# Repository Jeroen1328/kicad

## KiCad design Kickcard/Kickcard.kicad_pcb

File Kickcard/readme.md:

## The "KickCard": External Kickstart Freedom for the Amiga 500 🚀

The **KickCard** project was born out of a common frustration among **Amiga 500** enthusiasts: the hassle and motherboard variations involved in upgrading the internal **Kickstart ROM**. This external interface, connected via the Amiga 500's side expansion slot, offers a clean, versatile, and non-intrusive solution for using different Kickstart ROMs.

### Status
This project is **currently under construction** and has **not been tested** in a physical unit. The author is uncertain if a functional board will ultimately be built.

---

### Overcoming Internal ROM Challenges

Older Amiga 500 revisions required specific circuitry, often involving **pull-up resistors** on the data bus, to properly support certain **EPROMs** when used as the Kickstart ROM. Installing a new ROM meant opening the computer, desoldering (sometimes), and potentially adding components.

The KickCard eliminates this complexity. By providing an **external, standardized interface**, it bypasses the finicky requirements of various motherboard revisions, making ROM upgrades plug-and-play. Plus, you never have to **open your Amiga 500** just to swap a Kickstart version!

---

### Features and Functionality

Beyond its core function, the KickCard is a feature-rich expansion:

* **External Enable/Disable:** A DIP switch (**SW\_KICK**) allows the user to easily **enable or disable** the external KickCard ROM, reverting to the internal ROM if present.
* **Monitoring and Control (Optional):**
    * **Voltmeters:** Three optional **voltmeters** display the Amiga's crucial **+5V, +12V, and -12V** power supply lines, providing immediate diagnostic feedback.
    * **NMI/Reset Buttons:** Optional buttons for **$\overline{\text{INT7}}$ (Non-Maskable Interrupt)** and **System Reset** offer convenient control without needing a software-based utility.

---

### How the KickCard Works (The Logic)

The core of the KickCard's operation relies on a **GAL (Generic Array Logic)** chip and the Amiga's memory management architecture:

1.  **Initial Activation:** When the Amiga system starts up or is reset, a specific register, **$\overline{\text{OVL}}$ (Overlay)**, becomes active.
2.  **Memory Access Interception:** When the CPU addresses the **Kickstart memory range** ($000000-\text{07FFFF}$ and $\text{F80000}-\text{FFFFFF}$) with $\overline{\text{OVL}}$ active or ($\text{F80000}-\text{FFFFFF}$) with $\overline{\text{OVL}}$ not active, the GAL asserts the **$\overline{\text{OVR}}$ (Override)** signal.
3.  **Gary Disablement:** The asserted $\overline{\text{OVR}}$ signal prevents the **GARY** (Gate Array) chip—which typically manages memory arbitration—from responding to the bus, effectively taking control of the Kickstart address space.
4.  **Deactivation:** The $\overline{\text{OVL}}$ remains active until the CPU executes a write access to the address of the **CIA (Complex Interface Adapter)** chips. This action typically signals the completion of the basic system startup, and the GAL then makes the $\overline{\text{OVL}}$ register **inactive**, returning memory control to the standard system configuration.
5.  **when the roms is selected, the GAL also asserts the $\overline{\text{DTACK}}$ signal to tell the 68000 to complete the read cycle.
 
In essence, the KickCard *tricks* the Amiga into loading the Kickstart from the expansion port during the critical boot sequence, providing a robust and flexible ROM replacement solution.

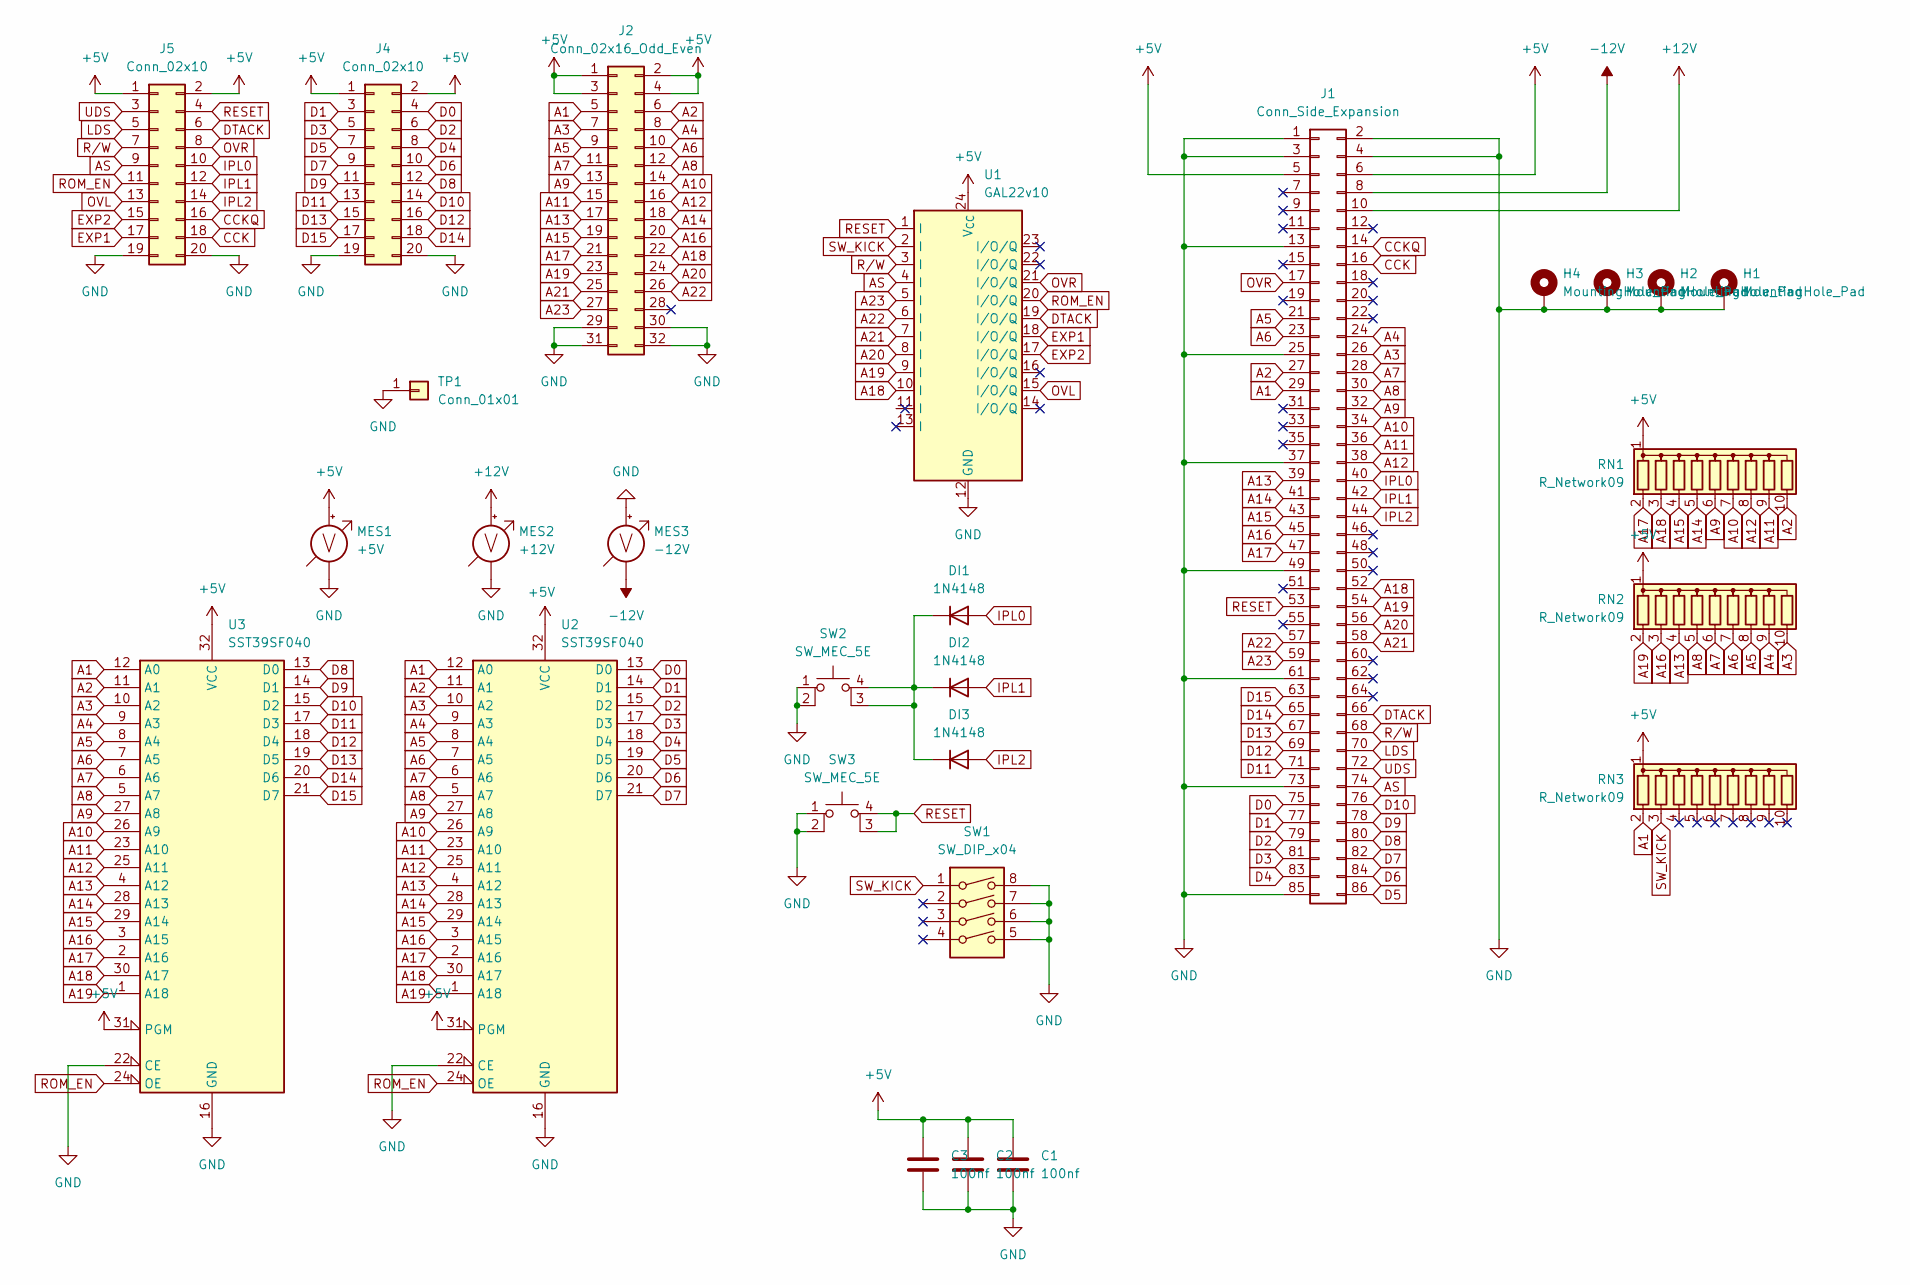
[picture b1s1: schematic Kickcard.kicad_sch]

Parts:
C1, C2, C3: 100nf; C_Disc_D3.0mm_W1.6mm_P2.50mm
DI1, DI2, DI3: 1N4148; D_DO-35_SOD27_P7.62mm_Horizontal
H1, H2, H3, H4: MountingHole_Pad; MountingHole_3.2mm_M3_Pad_Via
J1: Conn_Side_Expansion; Conn_Side_Expansion_Vertical
J2: Conn_02x16_Odd_Even; PinHeader_2x16_P2.54mm_Vertical
J4, J5: Conn_02x10; PinHeader_2x10_P2.54mm_Vertical
MES1: +5V; 0.28 voltmeter
MES2: +12V; 0.28 voltmeter
MES3: -12V; 0.28 voltmeter
RN1, RN2, RN3: R_Network09; R_Array_SIP10
SW1: SW_DIP_x04; SW_DIP_SPSTx04_Slide_6.7x11.72mm_W7.62mm_P2.54mm_LowProfile
SW2, SW3: SW_MEC_5E; Tactile Switch
TP1: Conn_01x01; TestPoint_Bridge_Pitch2.54mm_Drill1.0mm
U1: GAL22v10; DIP-24_W7.62mm
U2, U3: SST39SF040; DIP-32_W15.24mm

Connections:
+5V: C1.1, C2.1, C3.1, J1.5 (+5V), J1.6 (+5V), J2.1, J2.2, J2.3, J2.4, J4.1, J4.2, J5.1, J5.2, MES1.2 (+), RN1.1 (common), RN2.1 (common), RN3.1 (common), U1.24 (V_{CC}), U2.31 (PGM), U2.32 (VCC), U3.31 (PGM), U3.32 (VCC)
+12V: J1.10 (+12V), MES2.2 (+)
-12V: J1.8 (-5V), MES3.1 (-)
A1: J1.29 (A1), J2.5, RN3.2 (R1), U2.12 (A0), U3.12 (A0)
A2: J1.27 (A2), J2.6, RN1.10 (R9), U2.11 (A1), U3.11 (A1)
A3: J1.26 (A3), J2.7, RN2.10 (R9), U2.10 (A2), U3.10 (A2)
A4: J1.24 (A4), J2.8, RN2.9 (R8), U2.9 (A3), U3.9 (A3)
A5: J1.21 (A5), J2.9, RN2.8 (R7), U2.8 (A4), U3.8 (A4)
A6: J1.23 (A6), J2.10, RN2.7 (R6), U2.7 (A5), U3.7 (A5)
A7: J1.28 (A7), J2.11, RN2.6 (R5), U2.6 (A6), U3.6 (A6)
A8: J1.30 (A8), J2.12, RN2.5 (R4), U2.5 (A7), U3.5 (A7)
A9: J1.32 (A9), J2.13, RN1.6 (R5), U2.27 (A8), U3.27 (A8)
A10: J1.34 (A10), J2.14, RN1.7 (R6), U2.26 (A9), U3.26 (A9)
A11: J1.36 (A11), J2.15, RN1.9 (R8), U2.23 (A10), U3.23 (A10)
A12: J1.38 (A12), J2.16, RN1.8 (R7), U2.25 (A11), U3.25 (A11)
A13: J1.39 (A13), J2.17, RN2.4 (R3), U2.4 (A12), U3.4 (A12)
A14: J1.41 (A14), J2.18, RN1.5 (R4), U2.28 (A13), U3.28 (A13)
A15: J1.43 (A15), J2.19, RN1.4 (R3), U2.29 (A14), U3.29 (A14)
A16: J1.45 (A16), J2.20, RN2.3 (R2), U2.3 (A15), U3.3 (A15)
A17: J1.47 (A17), J2.21, RN1.2 (R1), U2.2 (A16), U3.2 (A16)
A18: J1.52 (A18), J2.22, RN1.3 (R2), U1.10 (I), U2.30 (A17), U3.30 (A17)
A19: J1.54 (A19), J2.23, RN2.2 (R1), U1.9 (I), U2.1 (A18), U3.1 (A18)
A20: J1.56 (A20), J2.24, U1.8 (I)
A21: J1.58 (A22), J2.25, U1.7 (I)
A22: J1.57 (A21), J2.26, U1.6 (I)
A23: J1.59 (A23), J2.27, U1.5 (I)
AS: J1.74 (_AS), J5.9, U1.4 (I)
CCK: J1.16 (XRDY), J5.18
CCKQ: J1.14 (_CCKQ), J5.16
D0: J1.75 (PD0), J4.4, U2.13 (D0)
D1: J1.77 (PD1), J4.3, U2.14 (D1)
D2: J1.79 (PD2), J4.6, U2.15 (D2)
D3: J1.81 (PD3), J4.5, U2.17 (D3)
D4: J1.83 (PD4), J4.8, U2.18 (D4)
D5: J1.86 (PD5), J4.7, U2.19 (D5)
D6: J1.84 (PD6), J4.10, U2.20 (D6)
D7: J1.82 (PD7), J4.9, U2.21 (D7)
D8: J1.80 (PD8), J4.12, U3.13 (D0)
D9: J1.78 (PD9), J4.11, U3.14 (D1)
D10: J1.76 (PD10), J4.14, U3.15 (D2)
D11: J1.71 (PD11), J4.13, U3.17 (D3)
D12: J1.69 (PD12), J4.16, U3.18 (D4)
D13: J1.67 (PD13), J4.15, U3.19 (D5)
D14: J1.65 (PD14), J4.18, U3.20 (D6)
D15: J1.63 (PD15), J4.17, U3.21 (D7)
DTACK: J1.66 (_DTACK), J5.6, U1.19 (I/O/Q)
EXP1: J5.17, U1.18 (I/O/Q)
EXP2: J5.15, U1.17 (I/O/Q)
GND: C1.2, C2.2, C3.2, H1.1, H2.1, H3.1, H4.1, J1.1 (GND), J1.2 (GND), J1.3 (GND), J1.4 (GND), J1.13 (GND), J1.25 (GND), J1.37 (GND), J1.49 (GND), J1.61 (GND), J1.73 (GND), J1.85 (GND), J2.29, J2.30, J2.31, J2.32, J4.19, J4.20, J5.19, J5.20, MES1.1 (-), MES2.1 (-), MES3.2 (+), SW1.5, SW1.6, SW1.7, SW1.8, SW2.1, SW2.2, SW3.1, SW3.2, TP1.1, U1.12 (GND), U2.16 (GND), U2.22 (CE), U3.16 (GND), U3.22 (CE)
IPL0: DI1.2 (A), J1.40 (_IPL0), J5.10
IPL1: DI2.2 (A), J1.42 (_IPL1), J5.12
IPL2: DI3.2 (A), J1.44 (_IPL2), J5.14
LDS: J1.70 (_LDS), J5.5
unnamed: DI1.1 (K), DI2.1 (K), DI3.1 (K), SW2.3 (K), SW2.4 (A)
OVL: J5.13, U1.15 (I/O/Q)
OVR: J1.17 (CDAC), J5.8, U1.21 (I/O/Q)
RESET: J1.53 (_RST), J5.4, SW3.3 (K), SW3.4 (A), U1.1 (I)
ROM_EN: J5.11, U1.20 (I/O/Q), U2.24 (OE), U3.24 (OE)
R/W: J1.68 (R_W), J5.7, U1.3 (I)
SW_KICK: RN3.3 (R2), SW1.1, U1.2 (I)
UDS: J1.72 (_UDS), J5.3

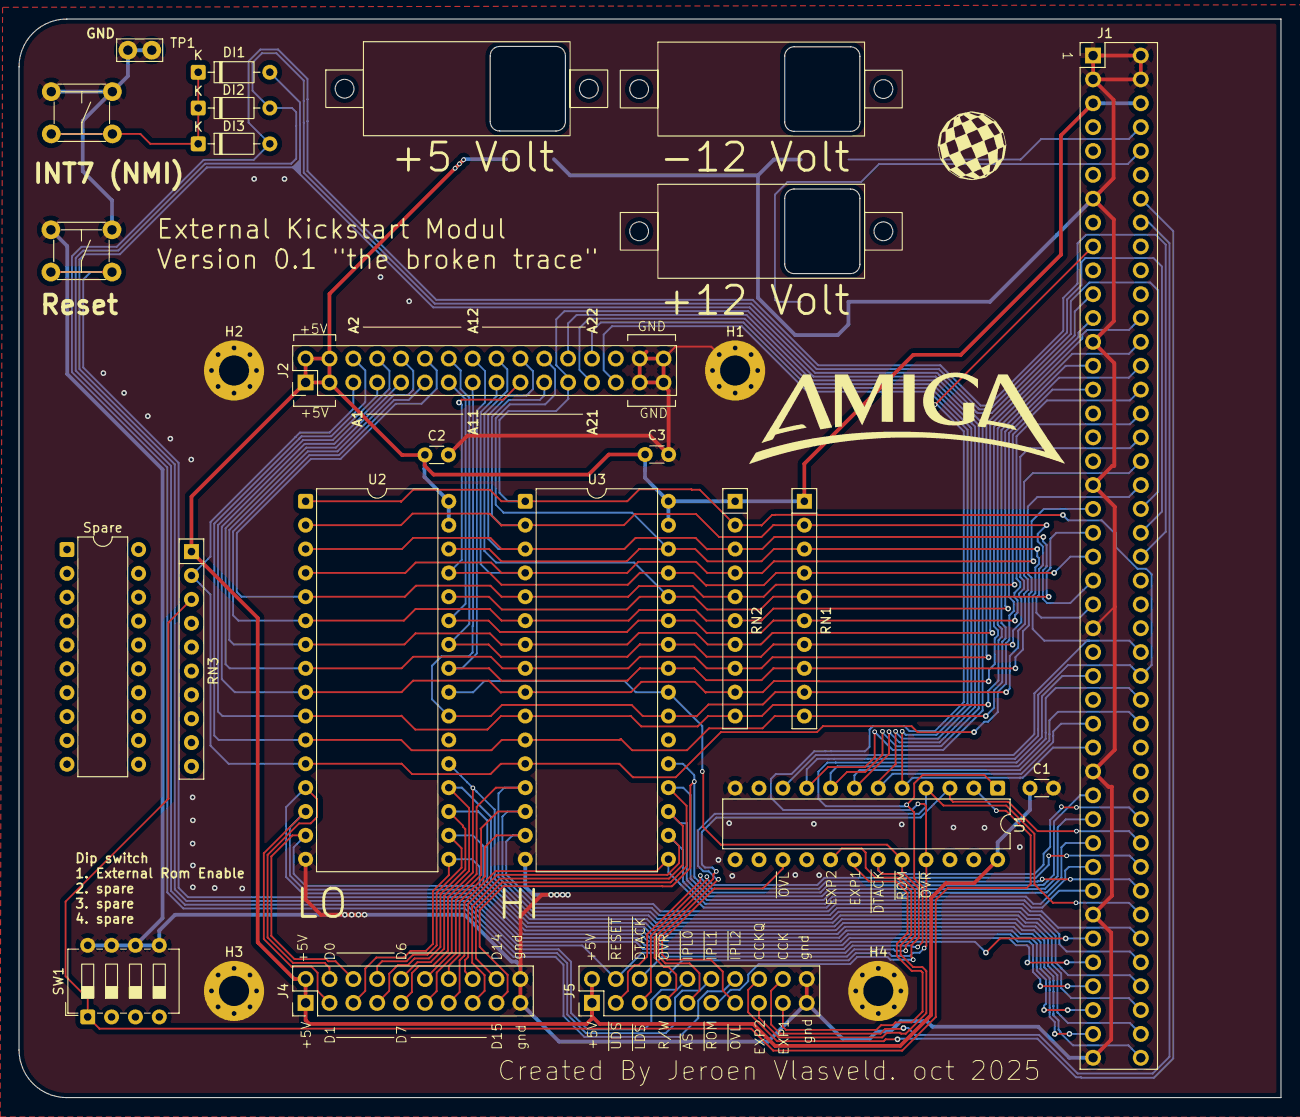
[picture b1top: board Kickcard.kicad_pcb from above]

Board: 2 copper layers, 134.3 x 114.8 mm, 28 parts (0 on the bottom side), 61 nets.

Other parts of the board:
Spare: DIP-20_W7.62mm

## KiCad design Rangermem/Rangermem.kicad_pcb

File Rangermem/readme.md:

## Amiga Rangermem Expansion

---

## Overview

The **Amiga Rangermem** is a memory expansion designed to sit **in-line** between the **Motorola 68000 CPU** and the **mainboard** of an **Amiga 500 (A500)** or **Amiga 500 Plus (A500+)**. This design provides an easy way to add fast, CPU-accessible "Ranger" memory (typically located in the $0xC00000$ to $0xD7FFFF$ range).

---

## Compatibility and Status

### Compatibility
While primarily designed for the A500/A500+, the principle of operation suggests this expansion **should also function with an Amiga 2000 (A2000)**. However, the author has not verified this, particularly concerning the necessary **physical clearance** inside the A2000's chassis.

### Status
This project is **currently under construction** and has **not been tested** in a physical unit. The author is uncertain if a functional board will ultimately be built.

---

## Theory of Operation

The expansion operates by intercepting and conditioning the signals between the CPU and the mainboard, primarily focusing on the **Address Strobe ($\overline{AS}$)** line.

### $\overline{AS}$ Interception

1.  The $\overline{AS}$ line, which signals that the address on the **address bus** is valid, is intercepted by the Rangermem board.
2.  **Mainboard Access:** If the address is **outside** the designated Ranger memory range, the $\overline{AS}$ signal is simply **passed through** to the mainboard, allowing normal operation.
3.  **Rangermem Access:** If the address is **within** the Ranger memory range, the $\overline{AS}$ signal is **blocked** from reaching the mainboard. Instead, the Rangermem generates both a **Data Acknowledge ($\overline{DTACK}$)** signal and a **ROM Select** signal to enable the on-board memory.

### $\overline{DTACK}$ Generation

* The $\overline{DTACK}$ signal tells the **68000 processor** that the data on the bus is ready.
* The Amiga mainboard normally relies on the **Gary** chip to generate $\overline{DTACK}$ when a mainboard resource is accessed.
* Since the Rangermem blocks the $\overline{AS}$ signal from reaching Gary for Ranger memory access, the expansion board **must generate its own $\overline{DTACK}$** pulse to complete the CPU's memory cycle.

### ROM/Memory Banks

* The expansion memory is divided into **three blocks of 512 KB**.
* These blocks can be individually enabled or disabled using **DIP switches** via the **ROM Select** lines generated by the expansion logic.

### Memory Detection

* **Kickstart's Search:** The **Kickstart ROM** searches for memory in the Ranger range **sequentially from the lowest address to the highest**.
* **Contiguity is Key:** If a lower-addressed block (e.g., Block 1) is **disabled**, the Kickstart will immediately **stop searching** for any further memory in that range. This means Blocks 2 and 3 will also not be automatically detected, even if they are enabled.
* To utilize blocks that are not automatically found during the initial system boot (either because of a disabled lower block or because they fall outside of the Kickstart's autoconfig range), a utility like **AddMem** must be used to manually add the memory to the system's map after booting.

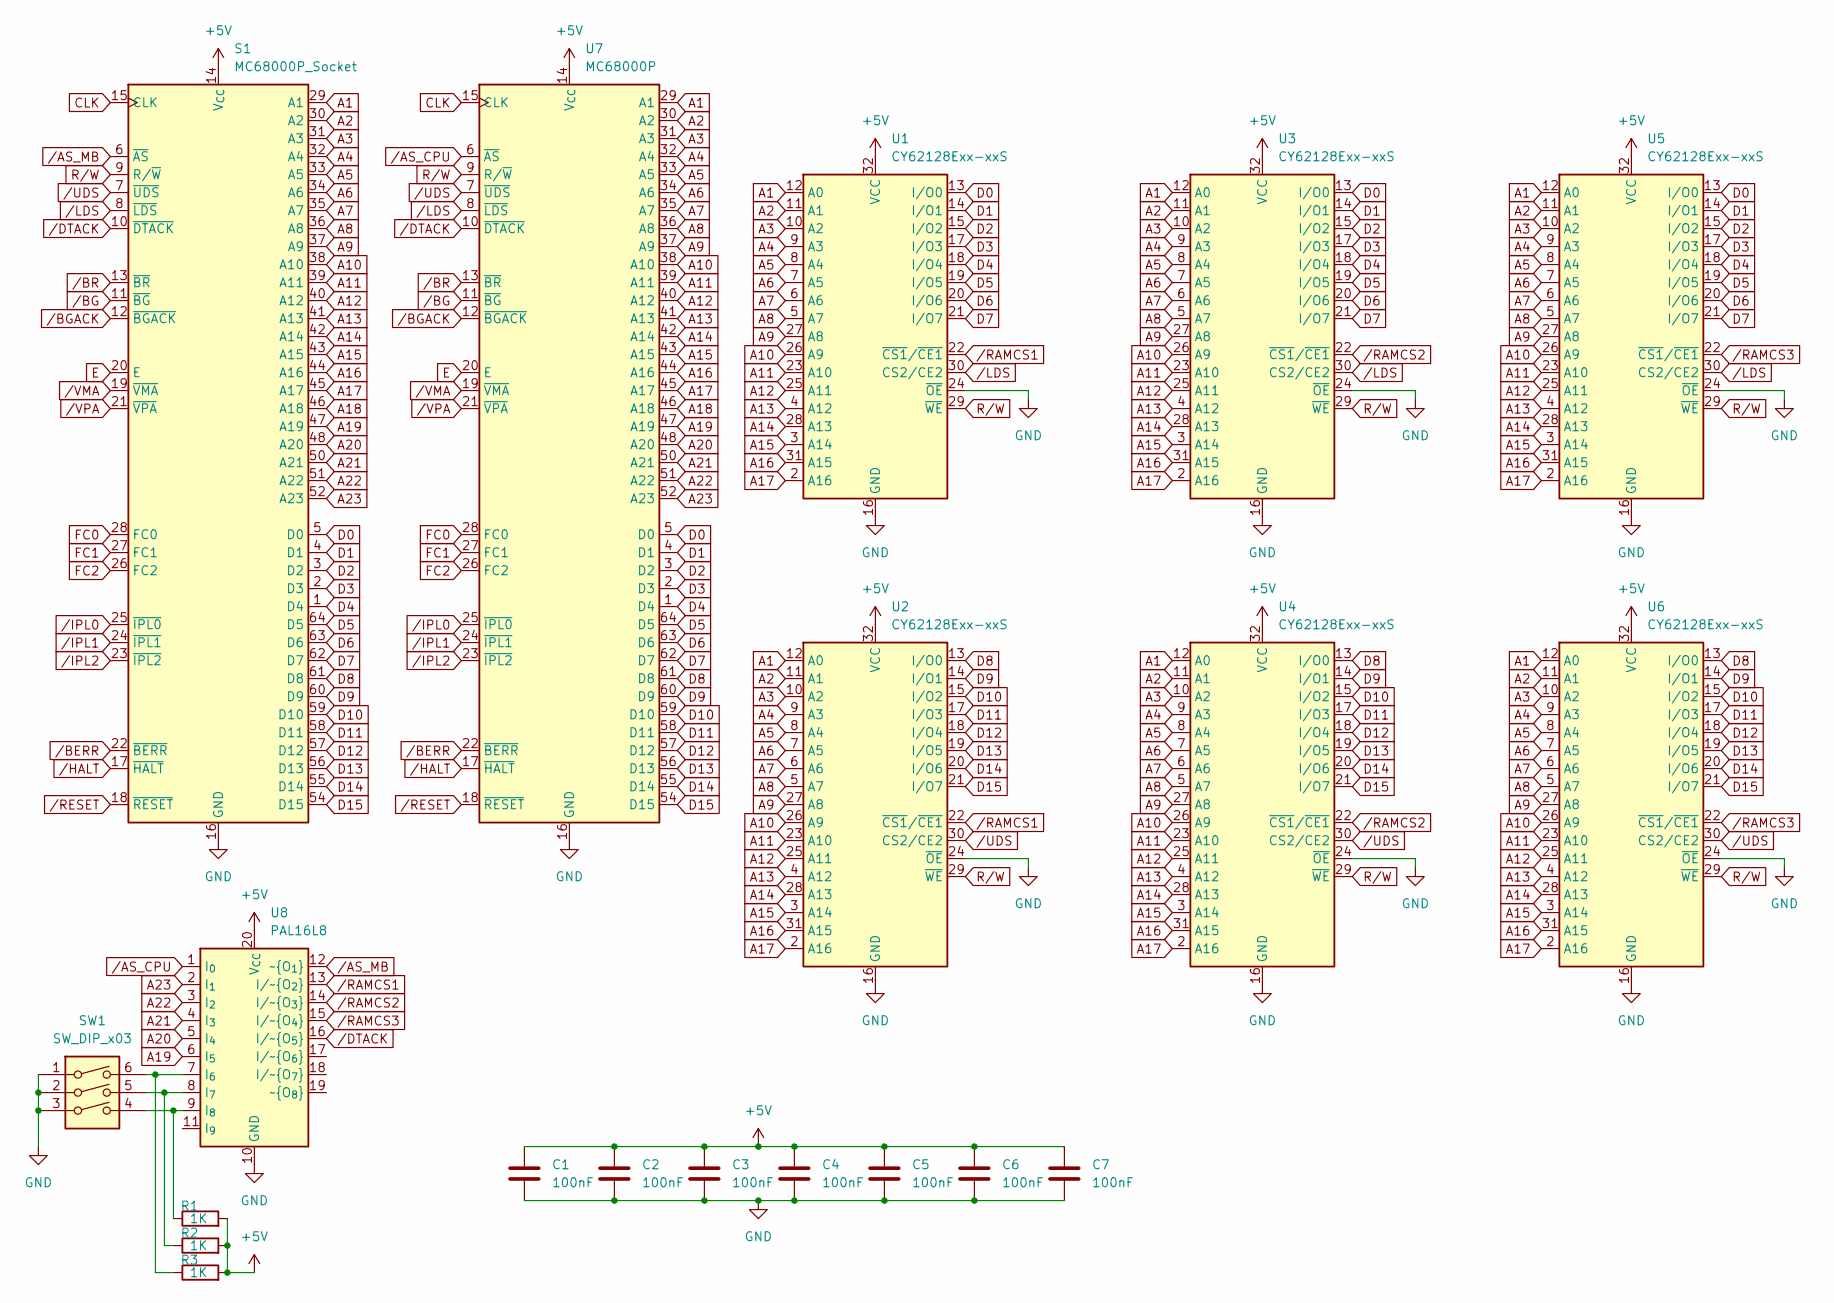
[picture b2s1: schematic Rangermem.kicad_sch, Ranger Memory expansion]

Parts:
C1, C2, C3, C4, C5, C6, C7: 100nF; C_Disc_D3.0mm_W1.6mm_P2.50mm
R1, R2, R3: 1K; R_Axial_DIN0204_L3.6mm_D1.6mm_P5.08mm_Horizontal
S1: MC68000P_Socket; DIP-64_W22.86mm
SW1: SW_DIP_x03; SW_DIP_SPSTx03_Slide_6.7x9.18mm_W7.62mm_P2.54mm_LowProfile
U1, U2, U3, U4, U5, U6: CY62128Exx-xxS; SOP-32_11.305x20.495mm_P1.27mm
U7: MC68000P; DIP-64_W22.86mm
U8: PAL16L8; DIP-20_W7.62mm

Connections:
+5V: C1.1, C2.1, C3.1, C4.1, C5.1, C6.1, C7.1, R1.2, R2.2, R3.2, S1.14 (V_{CC}), S1.49 (V_{CC}), U1.32 (VCC), U2.32 (VCC), U3.32 (VCC), U4.32 (VCC), U5.32 (VCC), U6.32 (VCC), U7.14 (V_{CC}), U7.49 (V_{CC}), U8.20 (V_{CC})
A1: S1.29 (A1), U1.12 (A0), U2.12 (A0), U3.12 (A0), U4.12 (A0), U5.12 (A0), U6.12 (A0), U7.29 (A1)
A2: S1.30 (A2), U1.11 (A1), U2.11 (A1), U3.11 (A1), U4.11 (A1), U5.11 (A1), U6.11 (A1), U7.30 (A2)
A3: S1.31 (A3), U1.10 (A2), U2.10 (A2), U3.10 (A2), U4.10 (A2), U5.10 (A2), U6.10 (A2), U7.31 (A3)
A4: S1.32 (A4), U1.9 (A3), U2.9 (A3), U3.9 (A3), U4.9 (A3), U5.9 (A3), U6.9 (A3), U7.32 (A4)
A5: S1.33 (A5), U1.8 (A4), U2.8 (A4), U3.8 (A4), U4.8 (A4), U5.8 (A4), U6.8 (A4), U7.33 (A5)
A6: S1.34 (A6), U1.7 (A5), U2.7 (A5), U3.7 (A5), U4.7 (A5), U5.7 (A5), U6.7 (A5), U7.34 (A6)
A7: S1.35 (A7), U1.6 (A6), U2.6 (A6), U3.6 (A6), U4.6 (A6), U5.6 (A6), U6.6 (A6), U7.35 (A7)
A8: S1.36 (A8), U1.5 (A7), U2.5 (A7), U3.5 (A7), U4.5 (A7), U5.5 (A7), U6.5 (A7), U7.36 (A8)
A9: S1.37 (A9), U1.27 (A8), U2.27 (A8), U3.27 (A8), U4.27 (A8), U5.27 (A8), U6.27 (A8), U7.37 (A9)
A10: S1.38 (A10), U1.26 (A9), U2.26 (A9), U3.26 (A9), U4.26 (A9), U5.26 (A9), U6.26 (A9), U7.38 (A10)
A11: S1.39 (A11), U1.23 (A10), U2.23 (A10), U3.23 (A10), U4.23 (A10), U5.23 (A10), U6.23 (A10), U7.39 (A11)
A12: S1.40 (A12), U1.25 (A11), U2.25 (A11), U3.25 (A11), U4.25 (A11), U5.25 (A11), U6.25 (A11), U7.40 (A12)
A13: S1.41 (A13), U1.4 (A12), U2.4 (A12), U3.4 (A12), U4.4 (A12), U5.4 (A12), U6.4 (A12), U7.41 (A13)
A14: S1.42 (A14), U1.28 (A13), U2.28 (A13), U3.28 (A13), U4.28 (A13), U5.28 (A13), U6.28 (A13), U7.42 (A14)
A15: S1.43 (A15), U1.3 (A14), U2.3 (A14), U3.3 (A14), U4.3 (A14), U5.3 (A14), U6.3 (A14), U7.43 (A15)
A16: S1.44 (A16), U1.31 (A15), U2.31 (A15), U3.31 (A15), U4.31 (A15), U5.31 (A15), U6.31 (A15), U7.44 (A16)
A17: S1.45 (A17), U1.2 (A16), U2.2 (A16), U3.2 (A16), U4.2 (A16), U5.2 (A16), U6.2 (A16), U7.45 (A17)
A18: S1.46 (A18), U7.46 (A18)
A19: S1.47 (A19), U7.47 (A19), U8.6 (I_{5})
A20: S1.48 (A20), U7.48 (A20), U8.5 (I_{4})
A21: S1.50 (A21), U7.50 (A21), U8.4 (I_{3})
A22: S1.51 (A22), U7.51 (A22), U8.3 (I_{2})
A23: S1.52 (A23), U7.52 (A23), U8.2 (I_{1})
CLK: S1.15 (CLK), U7.15 (CLK)
D0: S1.5 (D0), U1.13 (I/O0), U3.13 (I/O0), U5.13 (I/O0), U7.5 (D0)
D1: S1.4 (D1), U1.14 (I/O1), U3.14 (I/O1), U5.14 (I/O1), U7.4 (D1)
D2: S1.3 (D2), U1.15 (I/O2), U3.15 (I/O2), U5.15 (I/O2), U7.3 (D2)
D3: S1.2 (D3), U1.17 (I/O3), U3.17 (I/O3), U5.17 (I/O3), U7.2 (D3)
D4: S1.1 (D4), U1.18 (I/O4), U3.18 (I/O4), U5.18 (I/O4), U7.1 (D4)
D5: S1.64 (D5), U1.19 (I/O5), U3.19 (I/O5), U5.19 (I/O5), U7.64 (D5)
D6: S1.63 (D6), U1.20 (I/O6), U3.20 (I/O6), U5.20 (I/O6), U7.63 (D6)
D7: S1.62 (D7), U1.21 (I/O7), U3.21 (I/O7), U5.21 (I/O7), U7.62 (D7)
D8: S1.61 (D8), U2.13 (I/O0), U4.13 (I/O0), U6.13 (I/O0), U7.61 (D8)
D9: S1.60 (D9), U2.14 (I/O1), U4.14 (I/O1), U6.14 (I/O1), U7.60 (D9)
D10: S1.59 (D10), U2.15 (I/O2), U4.15 (I/O2), U6.15 (I/O2), U7.59 (D10)
D11: S1.58 (D11), U2.17 (I/O3), U4.17 (I/O3), U6.17 (I/O3), U7.58 (D11)
D12: S1.57 (D12), U2.18 (I/O4), U4.18 (I/O4), U6.18 (I/O4), U7.57 (D12)
D13: S1.56 (D13), U2.19 (I/O5), U4.19 (I/O5), U6.19 (I/O5), U7.56 (D13)
D14: S1.55 (D14), U2.20 (I/O6), U4.20 (I/O6), U6.20 (I/O6), U7.55 (D14)
D15: S1.54 (D15), U2.21 (I/O7), U4.21 (I/O7), U6.21 (I/O7), U7.54 (D15)
E: S1.20 (E), U7.20 (E)
FC0: S1.28 (FC0), U7.28 (FC0)
FC1: S1.27 (FC1), U7.27 (FC1)
FC2: S1.26 (FC2), U7.26 (FC2)
GND: C1.2, C2.2, C3.2, C4.2, C5.2, C6.2, C7.2, S1.16 (GND), S1.53 (GND), SW1.1, SW1.2, SW1.3, U1.16 (GND), U1.24 (~OE), U2.16 (GND), U2.24 (~OE), U3.16 (GND), U3.24 (~OE), U4.16 (GND), U4.24 (~OE), U5.16 (GND), U5.24 (~OE), U6.16 (GND), U6.24 (~OE), U7.16 (GND), U7.53 (GND), U8.10 (GND)
unnamed: R3.1, SW1.6, U8.7 (I_{6})
unnamed: R2.1, SW1.5, U8.8 (I_{7})
unnamed: R1.1, SW1.4, U8.9 (I_{8})
R/W: S1.9 (R/~W), U1.29 (~WE), U2.29 (~WE), U3.29 (~WE), U4.29 (~WE), U5.29 (~WE), U6.29 (~WE), U7.9 (R/~W)
/AS_CPU: U7.6 (~AS), U8.1 (I_{0})
/AS_MB: S1.6 (~AS), U8.12 (~O_{1})
/BERR: S1.22 (~BERR), U7.22 (~BERR)
/BG: S1.11 (~BG), U7.11 (~BG)
/BGACK: S1.12 (~BGACK), U7.12 (~BGACK)
/BR: S1.13 (~BR), U7.13 (~BR)
/DTACK: S1.10 (~DTACK), U7.10 (~DTACK), U8.16 (I/~O_{5})
/HALT: S1.17 (~HALT), U7.17 (~HALT)
/IPL0: S1.25 (~IPL0), U7.25 (~IPL0)
/IPL1: S1.24 (~IPL1), U7.24 (~IPL1)
/IPL2: S1.23 (~IPL2), U7.23 (~IPL2)
/LDS: S1.8 (~LDS), U1.30 (CS2/CE2), U3.30 (CS2/CE2), U5.30 (CS2/CE2), U7.8 (~LDS)
/RAMCS1: U1.22 (~CS1/~CE1), U2.22 (~CS1/~CE1), U8.13 (I/~O_{2})
/RAMCS2: U3.22 (~CS1/~CE1), U4.22 (~CS1/~CE1), U8.14 (I/~O_{3})
/RAMCS3: U5.22 (~CS1/~CE1), U6.22 (~CS1/~CE1), U8.15 (I/~O_{4})
/RESET: S1.18 (~RESET), U7.18 (~RESET)
/UDS: S1.7 (~UDS), U2.30 (CS2/CE2), U4.30 (CS2/CE2), U6.30 (CS2/CE2), U7.7 (~UDS)
/VMA: S1.19 (~VMA), U7.19 (~VMA)
/VPA: S1.21 (~VPA), U7.21 (~VPA)

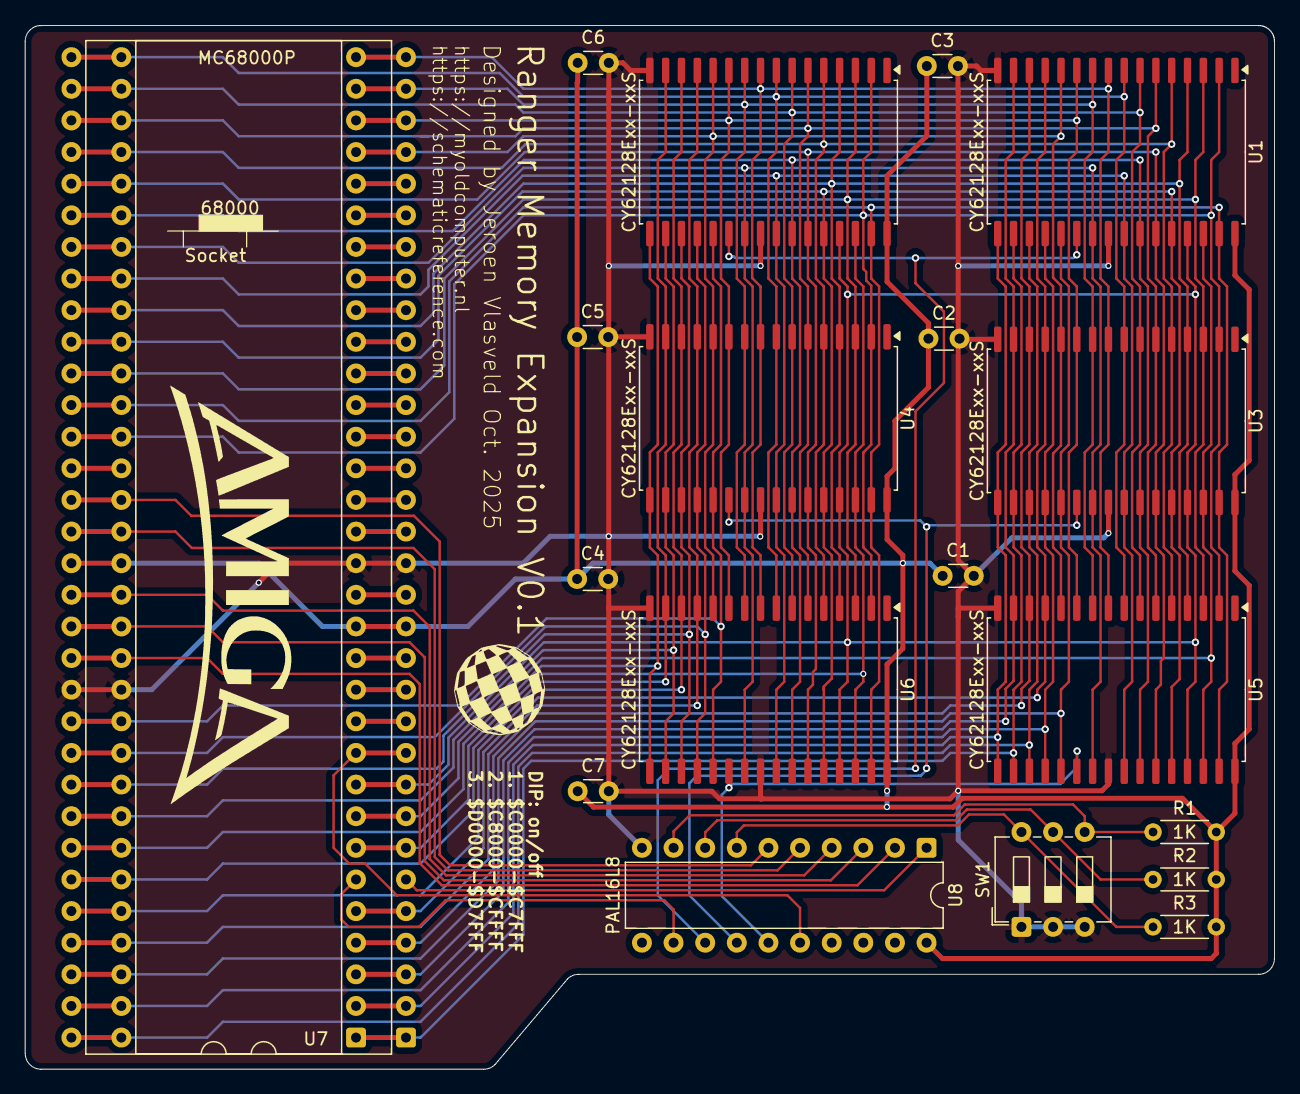
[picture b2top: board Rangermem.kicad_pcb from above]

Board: 2 copper layers, 100.3 x 83.8 mm, 20 parts (0 on the bottom side), 69 nets.

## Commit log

2025-09-28 initial
2025-09-28 added gal logic
2025-09-28 add gal
2025-09-29 corrected extension
2025-10-03 added test points
2025-10-06 added GND pads
    added GND pads to hook oscilloscope GND line
2025-10-17 Big Design change
    Remove test pins, extra rom and added "expansion" headers, corrected voltmeter footprint dimmensions
2025-10-17 initial
    an adapter to use A500 (and A1000 ?) side expansion in the coprocessor slot of the A2000, mainly designed to use the kickcard in the A2000
2025-10-17 AV Switch
2025-10-17 Updated gal
    removed old ABL file and added updated GAL files
2025-10-17 small update
    Added EXP1 and EXP2 ins from GAL to expansion header
2025-10-17 removed obsolete text
    removed obsolete text
2025-10-17 small update of track layout so gnd plane is better
    small update of track layout so gnd plane is better
2025-10-22 added fixing holes
